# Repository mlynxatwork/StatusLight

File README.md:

# StatusLight
Simple circuit board to light up a NeoPixel status light

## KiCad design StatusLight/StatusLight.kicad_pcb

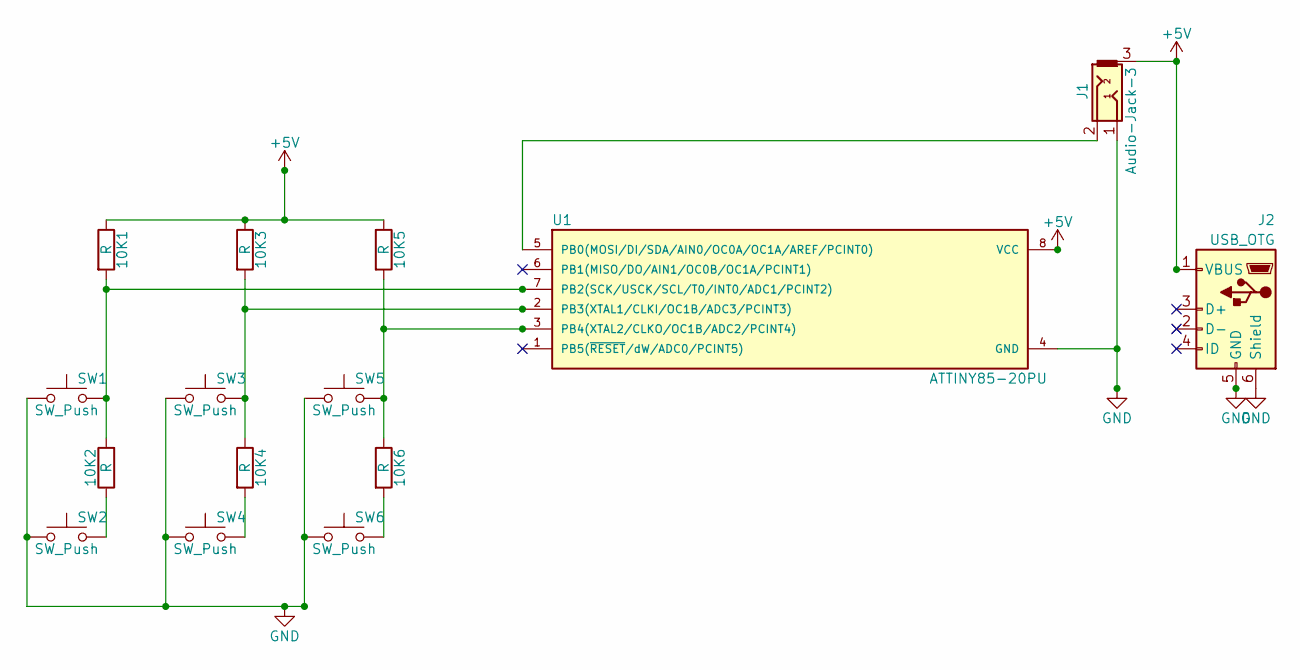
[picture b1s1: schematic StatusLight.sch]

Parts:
10K1, 10K2, 10K3, 10K4, 10K5, 10K6: R; R_Axial_DIN0207_L6.3mm_D2.5mm_P10.16mm_Horizontal
J1: Audio-Jack-3; SJ1-352XN
J2: USB_OTG; USB_Mini-B
SW1, SW2, SW3, SW4, SW5, SW6: SW_Push; CHERRY_PCB_100H
U1: ATTINY85-20PU; DIP-8_W7.62mm_LongPads

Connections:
+5V: 10K1.1, 10K3.1, 10K5.1, J1.3, J2.1 (VBUS), U1.8 (VCC)
GND: J1.1, J2.5 (GND), J2.6 (Shield), SW1.1, SW2.1, SW3.1, SW4.1, SW5.1, SW6.1, U1.4 (GND)
unnamed: 10K1.2, 10K2.2, SW1.2, U1.7 (PB2(SCK/USCK/SCL/T0/INT0/ADC1/PCINT2))
unnamed: 10K2.1, SW2.2
unnamed: 10K3.2, 10K4.1, SW3.2, U1.2 (PB3(XTAL1/CLKI/OC1B/ADC3/PCINT3))
unnamed: 10K4.2, SW4.2
unnamed: 10K5.2, 10K6.1, SW5.2, U1.3 (PB4(XTAL2/CLKO/OC1B/ADC2/PCINT4))
unnamed: 10K6.2, SW6.2
unnamed: J1.2, U1.5 (PB0(MOSI/DI/SDA/AIN0/OC0A/OC1A/AREF/PCI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)

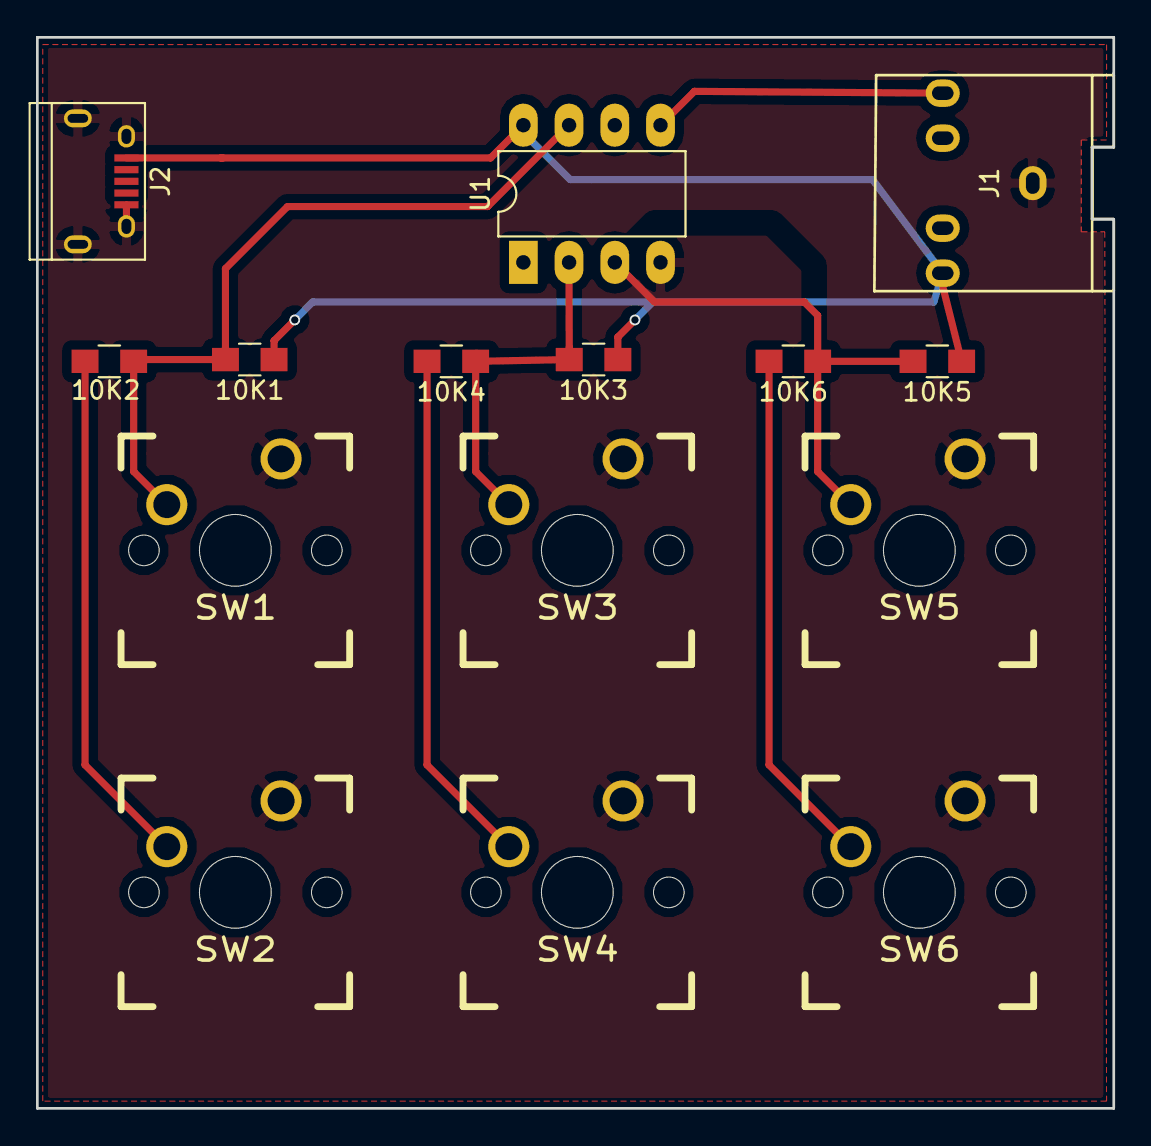
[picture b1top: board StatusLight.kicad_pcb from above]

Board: 2 copper layers, 59.8 x 59.5 mm, 15 parts (0 on the bottom side), 9 nets.

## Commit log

2017-08-16 Initial commit
    This includes a SMT version for Mathias switches and a through hole version for Cherry switches. I've not yet built the Mathias version although both sets of Gerbers (THT and Mathias) have been shipp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
2017-08-16 Adding the Arduino file
    Just to put everything in one place, this is the code needed to run the ATTiny85
2017-08-16 Labeled the button colors and sorted Red/Yello
